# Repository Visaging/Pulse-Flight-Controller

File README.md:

# PULSE Flight Controller
## Why "Pulse"?
The name is inspired by two things I love:
1.  **Pulse Width Modulation (PWM):** The heartbeat signal that powers every motor in this drone.
2.  **Beatbox:** A personal touch (look at the silkscreen artwork on the top layer).

## Overview
Pulse is a completely custom flight controller that was created from the ground up. I designed the whole stack myself to truly understand how a drone works, from the low-level motor mixing logic to the physics of the gyroscope, even though it would have been simpler to simply rely on off-the-shelf hardware and Betaflight. The custom PCB designs and the particular STM32 firmware I wrote to make the silicon work are both included in this repository, which acts as documentation for that process.

## Hardware Stack
* **MCU:** **STM32F405RGT6** - Chosen because it's a beast at math and has enough pins for everything.
* **IMU:** **ICM-42688-P** - Newer and cleaner noise performance than the old MPU6000.
* **Barometer:** **BMP280** - for altitude hold.
* **Gimbal Drivers:** 2x **DRV8313** - integrated directly on the FC.
    * Instead of a heavy separate gimbal controller board, I built the drivers right onto the FC to save weight and space.
* **Power System:** - Redesigned buck converter using **LMR14030SDDAR**.
  * I initially designed it for 6S (25.2V), but realized I wanted headroom. The new design handles up to **40V** input.

## The Firmware
### Key Features:
* **1kHz Control Loop:** A strict real-time scheduler runs the physics engine every 1ms.
* **Quad-X Mixing:** Takes PID output and mathematically mixes it for the 4 motors using **TIM8** (Timer).
* **Interrupt driven I/O:** The Receiver (UART3) and Telemetry (UART4/5) run in the background via Interrupts, so the main flight loop never "freezes" waiting for data.
* **Smart Telemetry:** Streams live voltage, angles, and state to a **Raspberry Pi** companion computer.

### How to Flash It
I added a **USB-C port** and the "Holy Trinity" of buttons (BOOT + RESET) to the PCB so I don't need external dongles.
1.  Plug in USB-C.
2.  Hold **BOOT**.
3.  Click **RESET**.
4.  Release **BOOT**.
5.  Flash the `.bin` file using **STM32CubeProgrammer** (USB DFU Mode).

--- 
<details>
  <summary><h2>PCB Schematics</h2></summary>

</details>

---
<details>
  <summary><h2>PCB Layout and Render</h2></summary>

## Layout
#### Overall:

---
#### Top Layer:

---
#### Layer 2:

---
#### Layer 3:

---
#### Bottom Layer:

---
#### Front Silkscreen:

---
#### Back Silkscreen:

---
## Render
#### Front:

---
#### Back:

</details>

--- 
## Bill of Material

| Item | Description | Quantity | Unit Price ($) | Total Price ($) | URL | Running Total ($) |
| ------------- | ------------- | ------------- | ------------- | ------------- | ------------- | ------------- |
| PCBA | PCB | 5 PCB, 1 PCBA | $216.41 | $216.41 | https://www.lioncircuits.com/ | $216.41  |
| Tactile Switches  | Boot and Reset Buttons | 2 | $0.0363 | $0.0726 | https://robu.in/product/ts6610tp-160gf-bxg-022-shou-han-50ma-100m%cf%89-100000-times-12v-160gf-round-button-standing-paste-spst-smd-tactile-switches-rohs/ | $216.4826 |
| TYPE-C-31-M-12 | USB-C Port | 1 | $0.42 | $0.42 | https://www.lioncircuits.com/ | $216.9026 |

<details>
  <summary>JLCPCB Order</summary>

</details>
<details>
  <summary>Lion Circuit Order</summary>

</details>
<details>
   
  <summary>Cart</summary>

</details>

## Lessons Learned
* **Power is hard:** My first schematic had a buck converter that would have fried on a 6S battery. Catching that mistake saved the project.
* **Routing matters:** Moving to 4 layers was scary at first, but it solved all my noise and heat issues.
* **Code vs. Reality:** Writing the firmware forced me to verify every single pin connection. I found out that "polling" a receiver is too slow, so I had to learn how Interrupts work.

## License: MIT

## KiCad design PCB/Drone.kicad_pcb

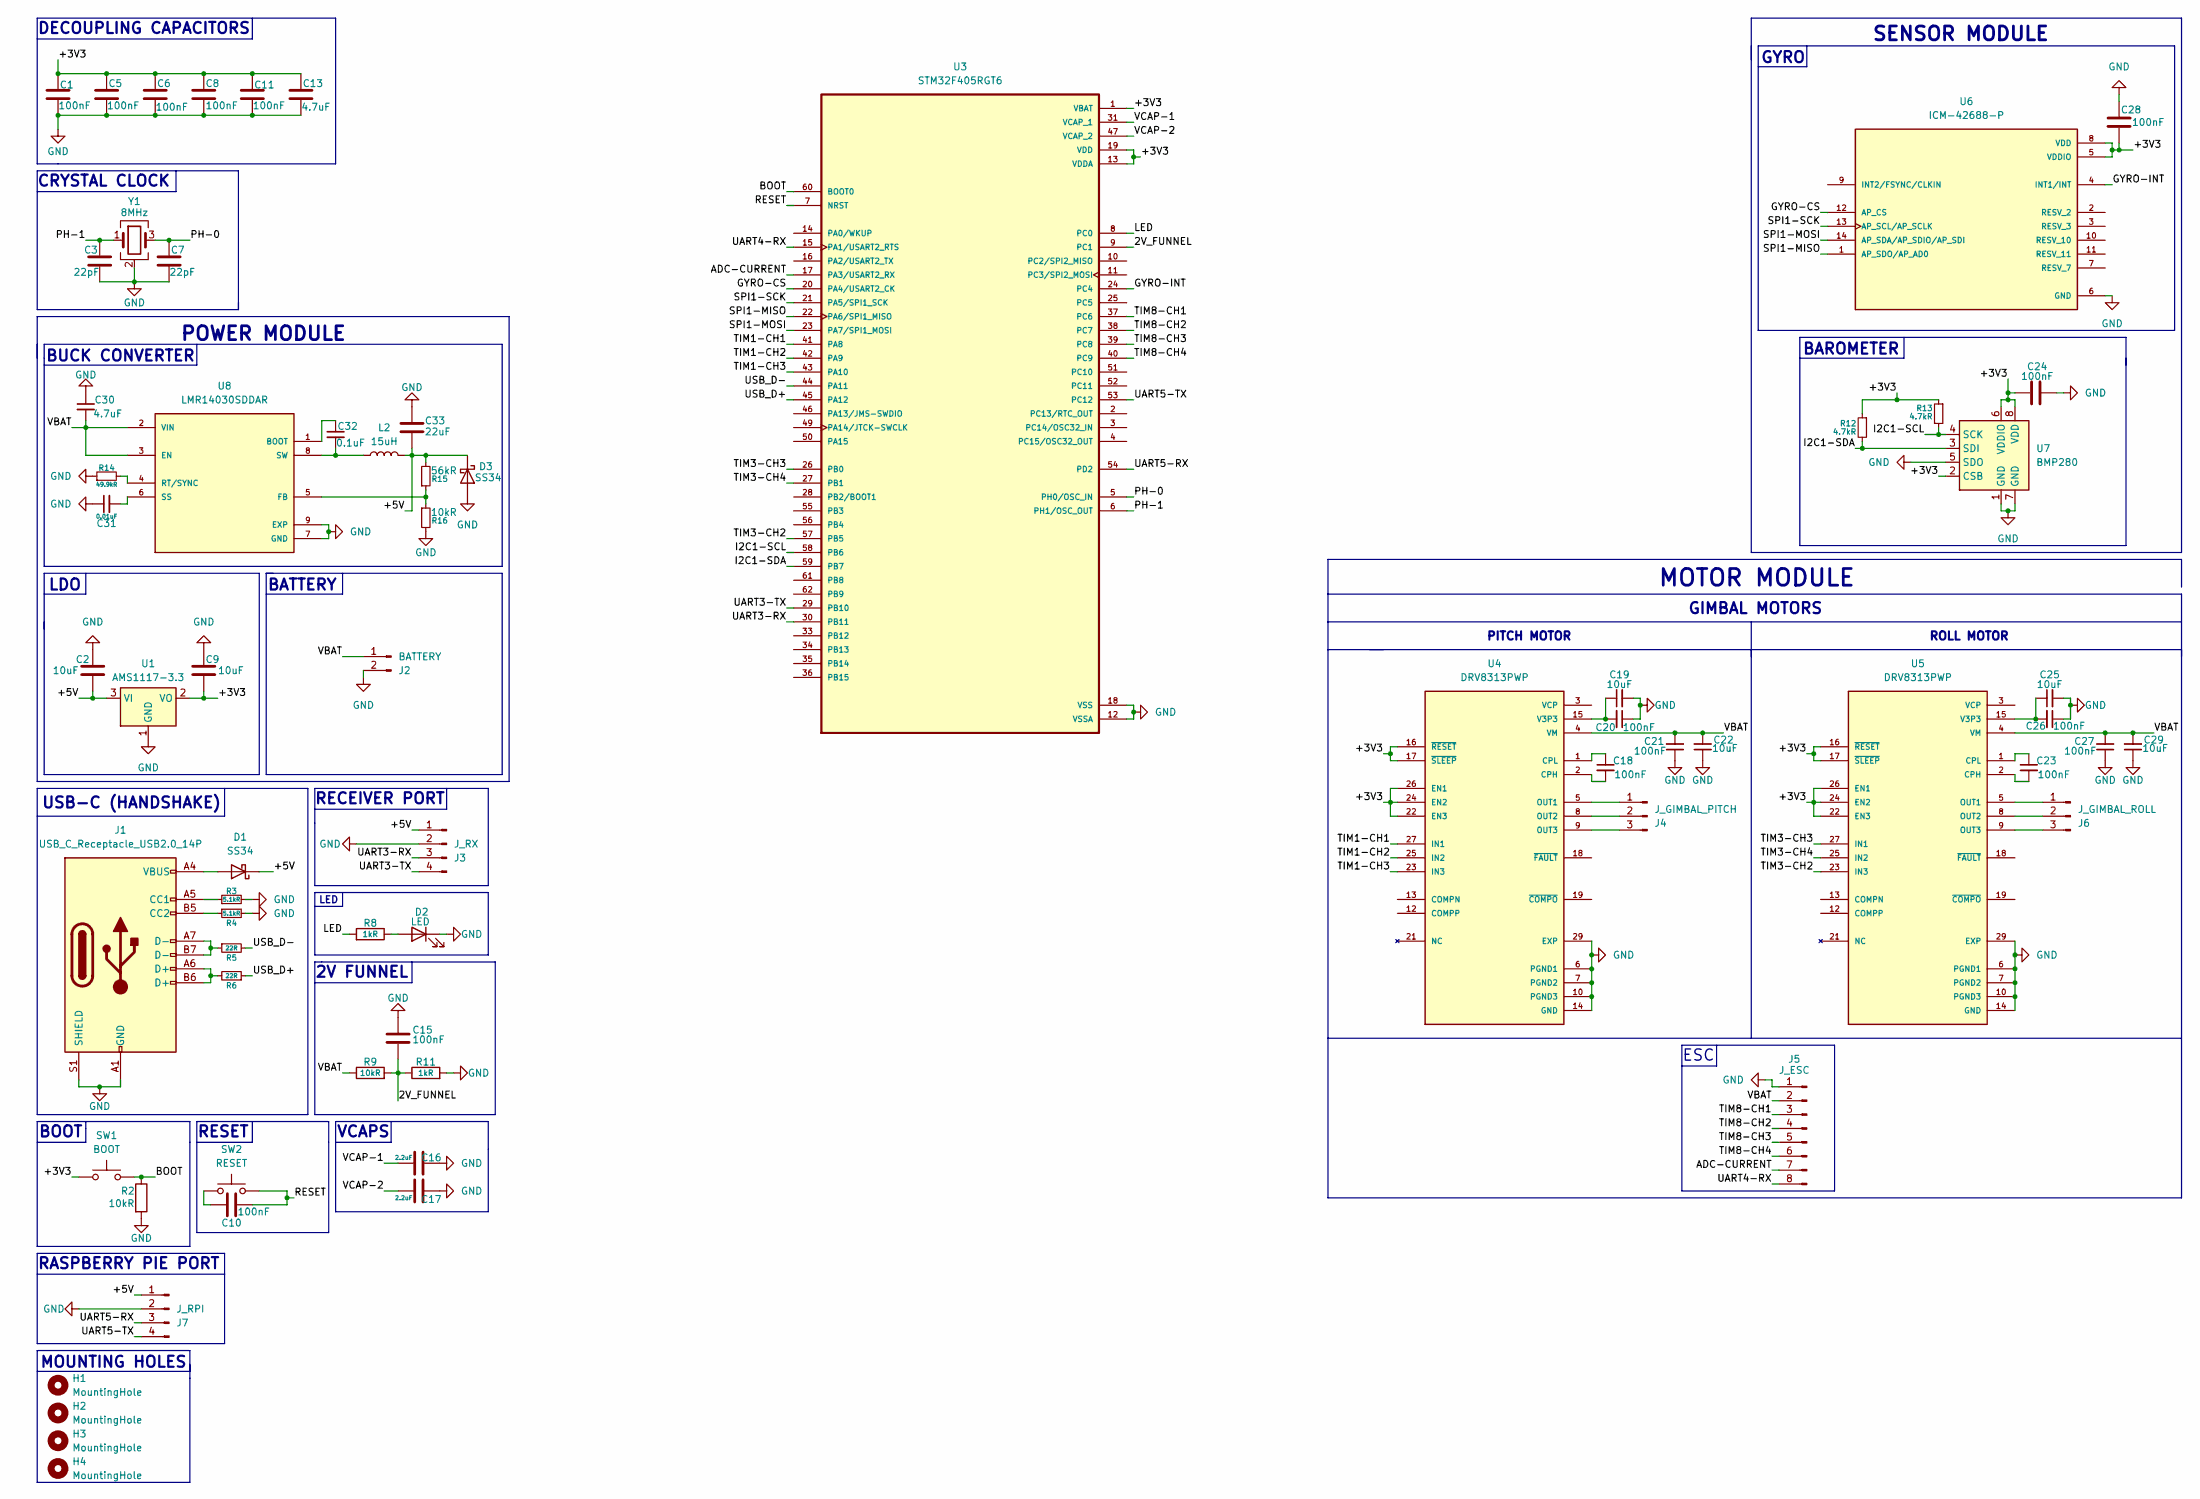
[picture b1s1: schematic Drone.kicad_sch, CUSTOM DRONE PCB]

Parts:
C1, C5, C6, C8, C10, C11, C15, C18, C20, C23, C24, C26, C28: 100nF; C_0603_1608Metric
C2, C9, C19, C25: 10uF; C_0603_1608Metric
C3, C7: 22pF; C_0603_1608Metric
C13: 4.7uF; C_0603_1608Metric
C16, C17: 2.2uF; C_0603_1608Metric
C21, C27: 100nF; C_1206_3216Metric
C22, C29: 10uF; C_1206_3216Metric
C30: 4.7uF; C_1210_3225Metric
C31: 0.01uF; C_0603_1608Metric
C32: 0.1uF; C_0603_1608Metric
C33: 22uF; C_1206_3216Metric
D1, D3: SS34; D_SMA
D2: LED; LED_0805_2012Metric
H1, H2, H3, H4: MountingHole; MountingHole_3.2mm_M3
J1: USB_C_Receptacle_USB2.0_14P; USB_C_Receptacle_HRO_TYPE-C-31-M-12
J2: BATTERY; SolderWire-2.5sqmm_1x02_P7.2mm_D2.4mm_OD3.6mm
J3: J_RX; PinHeader_1x04_P2.54mm_Vertical
J4: J_GIMBAL_PITCH; SolderWire-0.75sqmm_1x03_P4.8mm_D1.25mm_OD2.3mm
J5: J_ESC; PinHeader_1x08_P2.54mm_Vertical
J6: J_GIMBAL_ROLL; SolderWire-0.75sqmm_1x03_P4.8mm_D1.25mm_OD2.3mm
J7: J_RPI; SolderWire-0.1sqmm_1x04_P3.6mm_D0.4mm_OD1mm
L2: 15uH; L_Bourns_SRN6045TA
R2, R9: 10kR; R_0603_1608Metric
R3, R4: 5.1kR; R_0603_1608Metric
R5, R6: 22R; R_0603_1608Metric
R8, R11: 1kR; R_0603_1608Metric
R12, R13: 4.7kR; R_0603_1608Metric
R14: 49.9kR; R_0805_2012Metric
R15: 56kR; R_0805_2012Metric
R16: 10kR; R_0805_2012Metric
SW1: BOOT; SW_SPST_PTS645Sx43SMTR92
SW2: RESET; SW_SPST_PTS645Sx43SMTR92
U1: AMS1117-3.3; SOT-223-3_TabPin2
U3: STM32F405RGT6; QFP50P1200X1200X160-64N; PARTREV LTR
U4, U5: DRV8313PWP; SOP65P640X120-29N; PARTREV D
U6: ICM-42688-P; PQFN50P300X250X97-14N; PARTREV 1.2
U7: BMP280; Bosch_LGA-8_2x2.5mm_P0.65mm_ClockwisePinNumbering
U8: LMR14030SDDAR; SOIC127P600X170-9N; PARTREV A
Y1: 8MHz; Crystal_SMD_3225-4Pin_3.2x2.5mm

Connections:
/2V_FUNNEL: C15.2, R9.2, R11.1, U3.9 (PC1)
/+5V: C2.2, C33.2, D1.1 (K), D3.1 (K), J3.1, J7.1, L2.2, R15.2, U1.3 (VI)
/ADC-CURRENT: J5.7, U3.17 (PA3/USART2_RX)
/BOOT: R2.1, SW1.2, U3.60 (BOOT0); also elsewhere on the board
/GYRO-CS: U3.20 (PA4/USART2_CK), U6.12 (AP_CS)
/GYRO-INT: U3.24 (PC4), U6.4 (INT1/INT)
/I2C1-SCL: R13.2, U3.58 (PB6), U7.4 (SCK)
/I2C1-SDA: R12.2, U3.59 (PB7), U7.3 (SDI)
/LED: R8.2, U3.8 (PC0)
/PH-0: C7.1, U3.5 (PH0/OSC_IN), Y1.3
/PH-1: C3.1, U3.6 (PH1/OSC_OUT), Y1.1
/RESET: C10.2, SW2.2, U3.7 (NRST); also elsewhere on the board
/SPI1-MISO: U3.22 (PA6/SPI1_MISO), U6.1 (AP_SDO/AP_AD0)
/SPI1-MOSI: U3.23 (PA7/SPI1_MOSI), U6.14 (AP_SDA/AP_SDIO/AP_SDI)
/SPI1-SCK: U3.21 (PA5/SPI1_SCK), U6.13 (AP_SCL/AP_SCLK)
/TIM1-CH1: U3.41 (PA8), U4.27 (IN1)
/TIM1-CH2: U3.42 (PA9), U4.25 (IN2)
/TIM1-CH3: U3.43 (PA10), U4.23 (IN3)
/TIM3-CH2: U3.57 (PB5), U5.23 (IN3)
/TIM3-CH3: U3.26 (PB0), U5.27 (IN1)
/TIM3-CH4: U3.27 (PB1), U5.25 (IN2)
/TIM8-CH1: J5.3, U3.37 (PC6)
/TIM8-CH2: J5.4, U3.38 (PC7)
/TIM8-CH3: J5.5, U3.39 (PC8)
/TIM8-CH4: J5.6, U3.40 (PC9)
/UART3-RX: J3.3, U3.30 (PB11)
/UART3-TX: J3.4, U3.29 (PB10)
/UART4-RX: J5.8, U3.15 (PA1/USART2_RTS)
/UART5-RX: J7.3, U3.54 (PD2)
/UART5-TX: J7.4, U3.53 (PC12)
/USB_D+: R6.1, U3.45 (PA12)
/USB_D-: R5.2, U3.44 (PA11)
/VCAP-1: C16.1, U3.31 (VCAP_1)
/VCAP-2: C17.1, U3.47 (VCAP_2)
GND: C1.2, C2.1, C3.2, C5.2, C6.2, C7.2, C8.2, C9.1, C11.2, C13.2, C15.1, C16.2, C17.2, C19.2, C20.1, C21.1, C22.1, C24.1, C25.2, C26.1, C27.1, C28.1, C29.1, C30.1, C31.1, C33.1, D2.1 (K), D3.2 (A), J1.A1 (GND), J1.A12 (GND), J1.B1 (GND), J1.B12 (GND), J1.S1 (SHIELD), J2.2, J3.2, J5.1, J7.2, R2.2, R3.2, R4.2, R11.2, R14.1, R16.2, U1.1 (GND), U3.12 (VSSA), U3.18 (VSS), U3.63 (VSS), U4.6 (PGND1), U4.7 (PGND2), U4.10 (PGND3), U4.14 (GND), U4.20 (GND), U4.28 (GND), U4.29 (EXP), U5.6 (PGND1), U5.7 (PGND2), U5.10 (PGND3), U5.14 (GND), U5.20 (GND), U5.28 (GND), U5.29 (EXP), U6.6 (GND), U7.1 (GND), U7.5 (SDO), U7.7 (GND), U8.7 (GND), U8.9 (EXP), U8.V1 (EXP), U8.V2 (EXP), U8.V3 (EXP), U8.V4 (EXP), U8.V5 (EXP), U8.V6 (EXP), Y1.2 (G), Y1.4 (G)
unnamed 35: C10.1, SW2.1; also elsewhere on the board
unnamed: D1.2 (A), J1.A4 (VBUS), J1.A9 (VBUS), J1.B4 (VBUS), J1.B9 (VBUS)
unnamed: D2.2 (A), R8.1
unnamed: J1.A5 (CC1), R3.1
unnamed: J1.B5 (CC2), R4.1
unnamed: J1.A6 (D+), J1.B6 (D+), R6.2
unnamed: J1.A7 (D-), J1.B7 (D-), R5.1
unnamed 42: J4.1, U4.5 (OUT1); also elsewhere on the board
unnamed 43: J4.2, U4.8 (OUT2); also elsewhere on the board
unnamed 44: J4.3, U4.9 (OUT3); also elsewhere on the board
unnamed 45: J6.1, U5.5 (OUT1); also elsewhere on the board
unnamed 46: J6.2, U5.8 (OUT2); also elsewhere on the board
unnamed 47: J6.3, U5.9 (OUT3); also elsewhere on the board
unnamed: C18.2, U4.2 (CPH)
unnamed: C18.1, U4.1 (CPL)
unnamed: C19.1, C20.2, U4.15 (V3P3)
unnamed: C23.2, U5.2 (CPH)
unnamed: C23.1, U5.1 (CPL)
unnamed: C25.1, C26.2, U5.15 (V3P3)
unnamed: C32.1, U8.1 (BOOT)
unnamed: R15.1, R16.1, U8.5 (FB)
unnamed: R14.2, U8.4 (RT/SYNC)
unnamed: C31.2, U8.6 (SS)
unnamed: C32.2, L2.1, U8.8 (SW)
VDD: C1.1, C5.1, C6.1, C8.1, C9.2, C11.1, C13.1, C24.2, C28.2, R12.1, R13.1, SW1.1, U1.2 (VO), U3.1 (VBAT), U3.13 (VDDA), U3.19 (VDD), U3.32 (VDD), U3.48 (VDD), U3.64 (VDD), U4.16 (~RESET), U4.17 (~SLEEP), U4.22 (EN3), U4.24 (EN2), U4.26 (EN1), U5.16 (~RESET), U5.17 (~SLEEP), U5.22 (EN3), U5.24 (EN2), U5.26 (EN1), U6.5 (VDDIO), U6.8 (VDD), U7.2 (CSB), U7.6 (VDDIO), U7.8 (VDD); also elsewhere on the board
VM: C21.2, C22.2, C27.2, C29.2, C30.2, J2.1, J5.2, R9.1, U4.4 (VM), U4.11 (VM), U5.4 (VM), U5.11 (VM), U8.2 (VIN), U8.3 (EN)

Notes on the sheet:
RECEIVER PORT
BAROMETER
GIMBAL MOTORS
VCAPS
LED
BUCK CONVERTER
ESC
RESET
GYRO
CRYSTAL CLOCK
RASPBERRY PIE PORT
ROLL MOTOR
DECOUPLING CAPACITORS
PITCH MOTOR
LDO
2V FUNNEL
MOUNTING HOLES
BOOT
SENSOR MODULE
BATTERY
POWER MODULE
USB-C (HANDSHAKE)
MOTOR MODULE

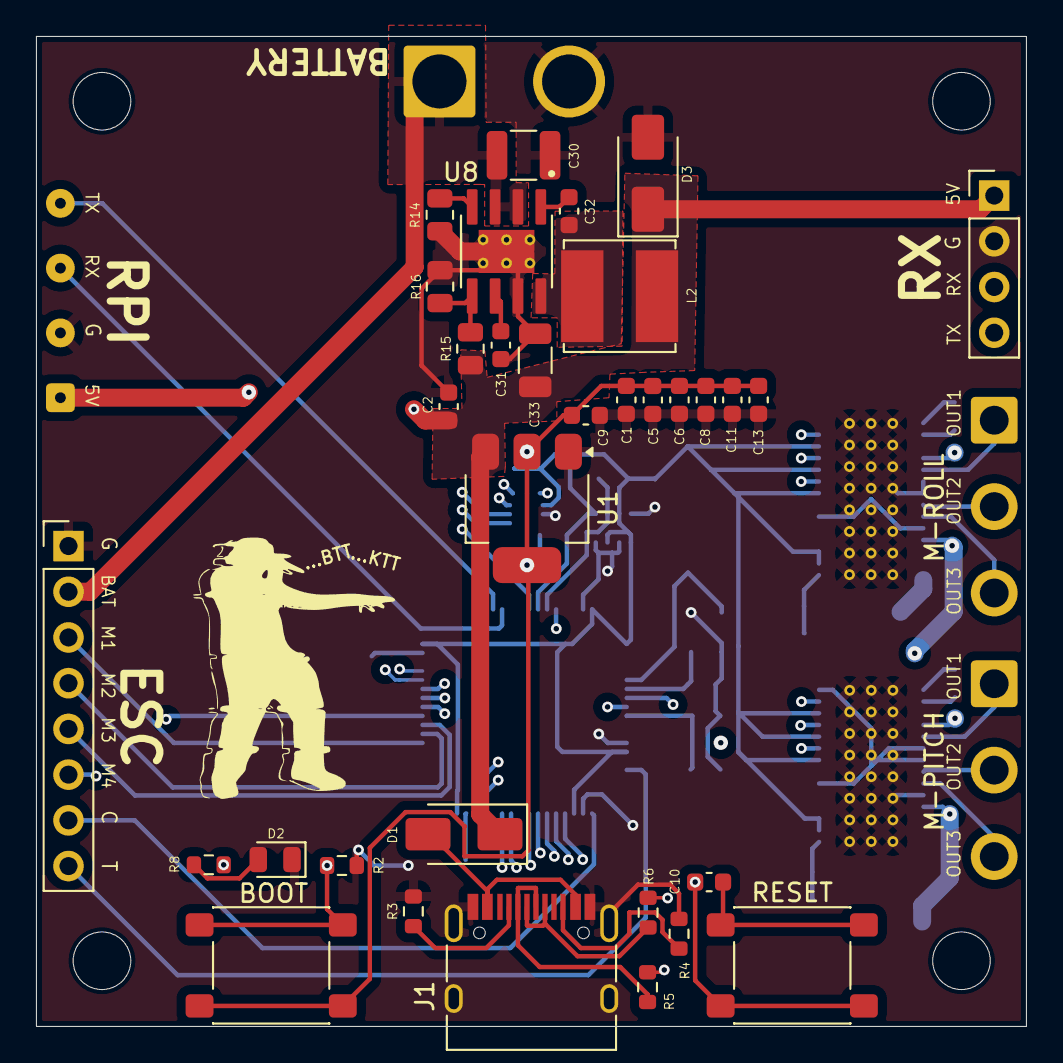
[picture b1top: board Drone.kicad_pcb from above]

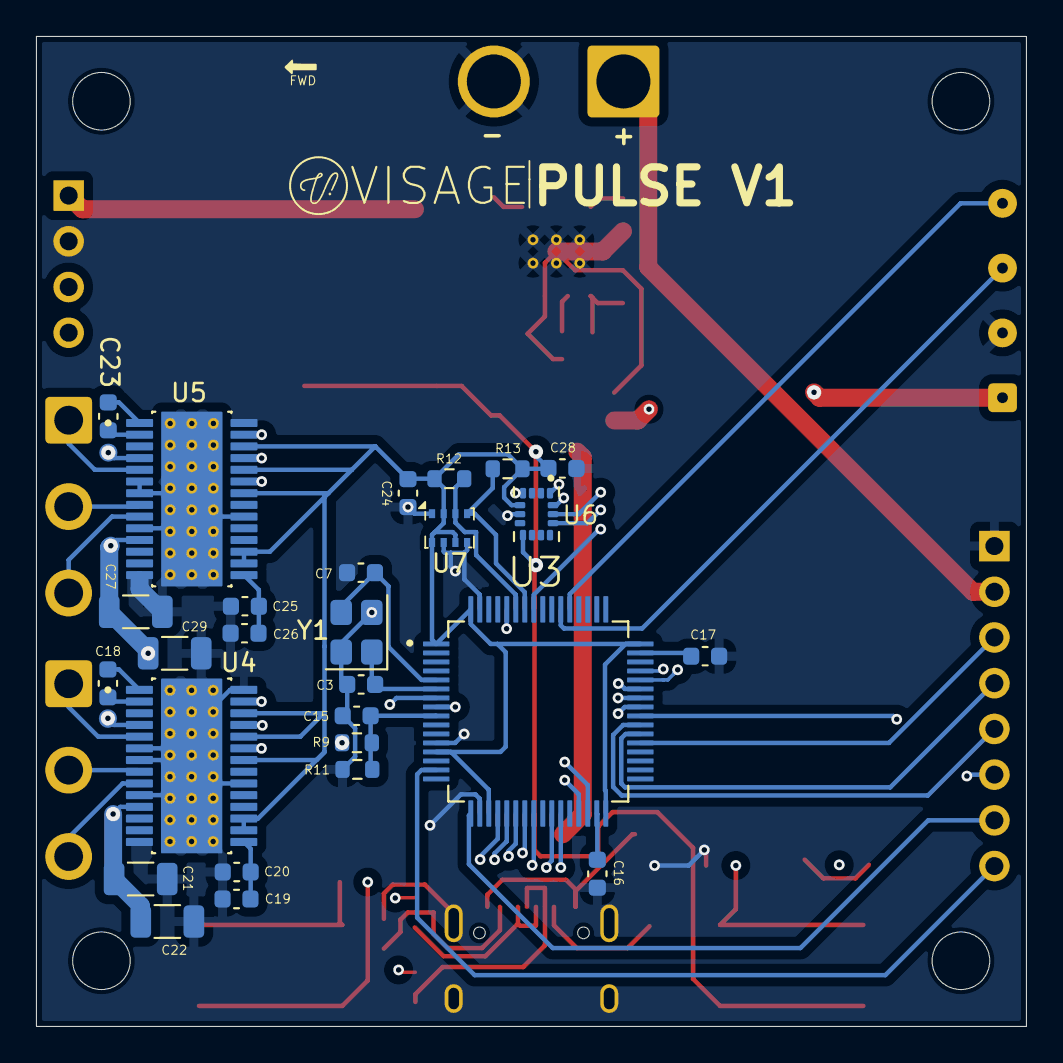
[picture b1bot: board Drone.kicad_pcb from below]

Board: 4 copper layers, 55.0 x 55.0 mm, 68 parts (27 on the bottom side), 61 nets.

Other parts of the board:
BOOT: BOOT; SW_SPST_PTS645Sx43SMTR92
M-PITCH: J_GIMBAL_PITCH; SolderWire-0.75sqmm_1x03_P4.8mm_D1.25mm_OD2.3mm
M-ROLL: J_GIMBAL_ROLL; SolderWire-0.75sqmm_1x03_P4.8mm_D1.25mm_OD2.3mm
RESET: RESET; SW_SPST_PTS645Sx43SMTR92

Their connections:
/BOOT: BOOT.2; also elsewhere on the board
/RESET: RESET.2; also elsewhere on the board
unnamed 35: RESET.1; also elsewhere on the board
unnamed 42: M-PITCH.1; also elsewhere on the board
unnamed 43: M-PITCH.2; also elsewhere on the board
unnamed 44: M-PITCH.3; also elsewhere on the board
unnamed 45: M-ROLL.1; also elsewhere on the board
unnamed 46: M-ROLL.2; also elsewhere on the board
unnamed 47: M-ROLL.3; also elsewhere on the board
VDD: BOOT.1; also elsewhere on the board

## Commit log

2026-02-03 Rename Visage_Pulse_Flight_Controller.bin to DEL
